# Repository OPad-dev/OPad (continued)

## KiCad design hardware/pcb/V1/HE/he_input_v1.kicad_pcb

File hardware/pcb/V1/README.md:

# OPad V1 PCBs

Modular hardware ecosystem joined by one 8-wire JST-SH cable:

| Board | Folder | Size | Status | What it does |
|---|---|---|---|---|
| **Controller carrier** | `Carrier/` | 35.0 × 48.2 mm, C-shaped | Production | Plugs onto the Waveshare ESP32-S3-Touch-LCD-2 headers and brings the module signals to a connector |
| **MX input module** | `MX/` | 52.0 × 24.0 mm | Production | Two Kailh MX mechanical hot-swap sockets under the key plate |
| **Hall Effect input module** | `HE/` | 52.0 × 24.0 mm | **v2 Experimental** | Two magnetic Rapid Trigger Hall sensors (TI DRV5055) under the key plate |

> [!IMPORTANT]
> The **Hall Effect module** requires firmware v2 (Rapid Trigger support), which is not yet available. V1.1 is built and its sensors work on the bench (2026-10-19, [`docs/specs/v2-hall-effect-design.md`](../../docs/specs/v2-hall-effect-design.md) §10b); the firmware's ADC sampling pipeline and Rapid Trigger engine are specified in [`docs/specs/v2-rapid-trigger.md`](../../docs/specs/v2-rapid-trigger.md). v1 firmware recognises an HE module by its ID voltage, shows a warning on the LCD and ignores key input rather than reading the analog sensor outputs as presses.

The input module is **swappable**: both the MX mechanical module and the Hall-effect (rapid trigger) module use the same outline, mounting holes, connector position and pinout, and plug into the same carrier and cable. The module reports which kind it is through an ID voltage on the connector (0.30 V for MX, 1.06 V for Hall Effect).

Production files live in each board's `production/` folder, one subfolder per fab: `jlcpcb/` (Gerbers, BOM, CPL), `pcbway/` (Gerbers with their order marker, BOM, centroid) and `aisler/` (native KiCad board and ODB++ with the parts in them). Renders, PDFs, STEP and the ERC/DRC reports sit next to them.

Status: the MX module and the carrier pass ERC, DRC and schematic parity in KiCad 10.0.6 with zero errors; the carrier has zero warnings, the MX module only "does not match copy in library" warnings, because its footprint and symbol copies were placed before `lib/` was rewritten by `gen_library.py` (same pads and pins; that board is built and working, so `export_production.py` accepts them). The Hall Effect module is generated and checked by its own toolchain (`scripts/he_board.py`, see below), which needs no KiCad install; it reports zero rule violations, its Gerbers verify clean against the netlist, and the generated KiCad files pass ERC and DRC with schematic parity in KiCad 10.0.6 (`scripts/check_he_kicad.py`; only "footprint does not match library" warnings remain, see Toolchain).

---

## Module connector (JST SH 8-pin, same on every input module)

| Pin | Net | Waveshare pin | GPIO | MX V1 use | Hall module use |
|---|---|---|---|---|---|
| 1 | 3V3 | P2-1 | – | pull-ups, ID divider | sensor supply |
| 2 | GND | P2-2 | – | switch common | ground |
| 3 | IN1 | P1-10 | **GPIO10** (ADC1_CH9) | KEY1 (left key) | analog 1 / SPI CS1 |
| 4 | IN2 | P1-9 | **GPIO7** (ADC1_CH6) | KEY2 (right key) | analog 2 / SPI CS2 |
| 5 | ID | P1-8 | GPIO8 (ADC1_CH7) | ID divider = 0.30 V | own ID voltage |
| 6 | IO6 | P1-3 | GPIO6 (ADC1_CH5) | not used | e.g. SPI MISO |
| 7 | IO4 | P1-2 | GPIO4 (ADC1_CH3) | not used | e.g. SPI MOSI |
| 8 | IO2 | P1-1 | GPIO2 (ADC1_CH1) | not used | e.g. SPI SCK |

- All six signals are ADC1 pins. On the ESP32-S3, ADC continuous (DMA) mode only supports ADC1 (see `docs/specs/v2-rapid-trigger.md` §2.2).
- SPI3 can be routed to any of these pins through the GPIO matrix. None of them are strapping pins, USB, UART0, or the touch/IMU I2C.
- The pin order is chosen so both boards route on two layers with no crossings.
- **Firmware:** in the app, set Key 1 = GPIO10 and Key 2 = GPIO7 (both are already in the allowed pin list). The hand-wired defaults (GPIO14 / GPIO9) don't apply to this board.

### Module ID

Each module has its own divider from 3V3 to GND on ID. The carrier has no parts on this line.

| Module | Top resistor | Bottom resistor | ID voltage |
|---|---|---|---|
| MX V1 | 100 kΩ (R3) | 10 kΩ (R4) | 0.30 V |
| **Hall Effect V1** | **100 kΩ (R1)** | **47 kΩ (R2)** | **1.06 V** |
| reserved: Hall SPI | 100 kΩ | 100 kΩ | 1.65 V |

The divider's source impedance is 100k ∥ 47k ≈ 32 kΩ, above the ~10 kΩ the ESP32-S3 ADC likes. ID is read once at start-up, so average a handful of samples instead of trusting a single conversion.

With no module plugged in, GPIO8 floats. The firmware can enable the internal pull-down to read about 0 V in that case.

---

## MX input module (`MX/`)

- **Case coordinates** below are those of `hardware/3d/custom_case/V1/osupad_enclosure.scad`: origin at the front-left outer corner, X to the right, Y toward the screen. KiCad uses X = 100 + case X and Y = 100 − case Y, so the top of the KiCad editor is the rear of the case and the layout is not mirrored.
- **Key centres:** case (28.475, 16.5) and (47.525, 16.5), 19.05 mm pitch, the same as the plate cutouts.
- **Outline:** case X 12…64, Y 7…31, 1.5 mm corner radius.
- **Mounting holes:** 2× M2 (2.2 mm NPTH) at case (15.5, 16.5) and (60.5, 16.5), on the key axis and clear of the switch footprints. The PCB must be held there, or it moves when a switch is pulled. Case V1.1 does this without screws: pins in the key deck go through the holes and posts on the bottom plate clamp the PCB against the deck.
- **Height:** the PCB top is **5.0 mm below the top of the plate** (plate 1.5 mm, case z = 10.0). About 3.5 mm of free space is needed under the PCB bottom for the sockets (1.85 mm) and J1 (2.9 mm).
- **Everything is on the bottom side** (sockets, J1, R1–R4, C1), so JLCPCB assembles one side only. The switches go in from the top through the plate.
- **J1** sits at the rear edge, centred on the keys, with the opening facing the screen. The cable leaves toward the controller.
- **Footprint:** `lib/osupad.pretty/Kailh_CPG151101S11_MX_Hotswap_Bottom` is the Kailh land pattern (3.05 mm pin holes, 4.0 mm centre, 1.75 mm pegs, 2.55 × 2.5 mm pads), drawn from the socket side and placed flipped. The switch pins point to the rear (standard orientation).

## Hall Effect input module (`HE/`)

Same outline, mounting holes, connector position and pinout as the MX module, so the two are interchangeable on one cable. Instead of switching a pin to ground, each key has a **TI DRV5055A3 ratiometric linear Hall sensor** whose analog output tracks the magnet in the switch stem, which is what rapid trigger needs.

> **V1.0 erratum (fixed in V1.1):** the V1.0 SOT-23 footprint was mirrored, so every assembled sensor sits with **VCC on its IN line and OUT on 3V3**. It powers itself backwards through its protection diode, reads a fixed ~2.9 V and barely reacts to a magnet. The connectivity was right, so neither DRC nor the assembler could catch it. V1.1 swaps pads 1 and 2 (`scripts/gen_library.py`, `scripts/he_board.py`), moves C2/C3 to the pin-1 side so the 3V3 stub and the IN line do not cross, and `he_board.py`'s self-test now checks every SOT-23's pin order against the real package. A V1.0 board works only with each sensor re-soldered upside down (marking towards the board), which mirrors its pin order back.
>
> **V1.1 review (2026-10-10), before ordering:** TI's DBZ pinout (datasheet SBAS640C Figure 4-1 and Table 4-1: 1 = VCC, 2 = OUT, 3 = GND, pin 1 top-left in the top view) was checked against the footprint by hand, against KiCad's flip convention and against the V1.0 measurements; the three agree with the V1.1 pads. Found and fixed in the same pass: the vias grow from 0.6 to **0.7 mm** (0.2 mm annular ring, which Aisler's HASL rules and Eurocircuits' class 6 need; JLCPCB accepted 0.6); the silkscreen square round each sensor was 3.0 mm and crossed the pad tips, it is now 3.6 mm with a pin-1 dot, and `C2`/`C3` moved 0.2 mm away from the sensors to make room; the pour gap went from 0.3 to 0.45 mm and a ground via fills the pocket next to U2, so the Gerbers hold no floating copper slivers (`verify_he_gerbers.py` now checks for islands); the generated schematic had an unescaped quote and did not load in KiCad, so ERC had never actually run on it (it now passes, with PWR_FLAGs and a connector symbol that carries the MP pads). None of these change the netlist.

### Sensor architecture (the part that matters)

This is **Architecture A: bottom-side SMT on solid FR-4.**

- There is **no 4.0 mm stem hole** at the key centres. `SW_MX_Hall_PlateMount` (used for a through-hole stem) is *not* the footprint here; `SW_MX_Hall_PlateMount_SolidCentre` is, and it contributes only the two alignment peg holes.
- U1 and U2 are centred **exactly** on the key centres (16.475, 9.5) and (35.525, 9.5), on the bottom copper, directly under the magnet.
- A **3.0 × 3.0 mm copper keepout on both layers** around each sensor keeps the ground pour out of the magnetic path, so the stem magnet's flux is not damped by eddy currents in the plane. In KiCad these are rule areas with `copperpour not_allowed`; in the Gerbers the pour is genuinely absent there.
### Why there is no centre hole, and what the board is actually compatible with

In a Lekker / Gateron KS-20 class magnetic switch (Gateron's KS-20T drawing DS-02-001-A0, in the [Magnetic Orange datasheet](https://gateron.com/u_file/2312/26/file/GATERONMagneticOrangeSwitch-KS-20TO10B050NW-Y64.pdf), sheet 1):

- **the magnet sits in the stem at the switch centre, N pole towards the PCB.** There is no MX-style centre pole and no 4 mm centre hole;
- **two Ø 1.70 ± 0.05 mm plastic pins, 10.16 mm apart (±5.08 mm), stick out of the bottom and pass straight through the PCB**, protruding about 1 mm out the back. That is why the 1.75 mm peg holes are needed;
- the bottom housing has a pocket ("the hole for setting hall sensor") so Gateron's own reference layout puts a SOT-23 sensor on the **top** of the PCB, between the two pins, with three 0.8 × 0.8 mm pads.

So a top-side sensor is possible with these switches; this board puts it on the bottom instead, like Wooting ([Lekker update #5, part 2](https://wooting.io/post/we-overcame-the-challenges-lekker-update-5-part-22)), because single-side assembly is cheaper and the top of the PCB stays flat against the plate. The price is distance: the magnet reads through the full 1.6 mm of FR-4 plus the package, so the field at the die is a fraction of what Gateron's pocket position sees (numbers under Sensor sensitivity). Peg holes **and** a solid centre **and** a bottom-side sensor is a consistent set; a board that had the peg holes *and* a 4 mm centre hole would be an MX PCB-mount pattern, which is a different switch.

| Switch | Works on this board? |
|---|---|
| Gateron KS-20 / Wooting Lekker, KS-37 / Magnetic Jade, Geon Raw HE and other Lekker-standard magnetic switches | Yes — flush magnet centre, two ±5.08 mm plastic pins |
| Switches sold as "**TMR switches**" | Yes — see below |
| MX mechanical (Cherry, Gateron, Kailh…) | **No.** A real MX switch has a centre pole and metal pins. That is what the `MX/` module is for — same outline, same connector, swap the module |

**On "TMR switches":** TMR (tunnel magnetoresistance) is a *sensor* technology that lives on the keyboard's PCB, not a different kind of switch. A switch marketed as a "TMR switch" is the same magnetic switch — a magnet in an MX-form stem with a flush bottom and two pins — and the industry uses them interchangeably: Gateron Jade, Jade Pro and Lekker V2 all go into Hall boards like the Wooting 60HE and TMR boards like the Womier SK75 alike. This module reads the magnet with a Hall sensor, and the magnet does not know or care what sensor is underneath it, so TMR-branded switches drop straight in.

Two caveats, neither of which is a fit problem:

- **Magnet strength varies by switch model.** TMR sensors are far more sensitive than Hall, so a vendor *can* pair a TMR-targeted switch line with a weaker magnet. If you use such a switch here, A3 is the wrong variant and you want A1 or A2. As Wooting put it, what matters is matching the sensitivity range to the magnet, not chasing sensitivity for its own sake.
- **This board cannot be rebuilt with a TMR sensor as a drop-in.** The common analog TMR parts (MultiDimension TMR2001, TMR2083) are SOT-23-**5**, not the 3-pin SOT-23 used here, so they would need a new footprint and a re-route. Most TMR designs also mount the sensor *off-axis*; U1/U2 here are deliberately on-axis at the key centre, which is the right placement for the DRV5055.

These magnetic switches are deliberately not MX-compatible; vendors say so themselves. The claim this board makes is "every switch in the Lekker standard", not "every keyboard switch ever made". If a magnetic switch turns up with a protruding MX-style centre pole, it will foul the sensor and is out of scope for V1 — I found no current HE switch that does this, since the whole class puts the magnet where that pole would be.

### Sensor sensitivity

The magnet reads through 1.6 mm of FR-4, so the field at the die is weaker than a top-side design's. Wooting hit the same geometry and compensated with a stronger magnet *and* a more sensitive sensor. All three variants share the SOT-23 pinout and this footprint, so **the board never changes** — only which reel JLCPCB loads. Set `SENSOR_VARIANT` in `scripts/he_board.py` and regenerate.

Datasheet values (TI SBAS640C §5.6, VCC = 3.3 V, 25 °C): quiescent output 1.59–1.71 V (typ. 1.65 V), linear output range 0.2 V to VCC − 0.2 V, input-referred noise 0.2 mT peak-to-peak for every variant (so a more sensitive part gives more volts per millimetre but the same magnetic noise):

| Variant | LCSC | Sensitivity @3.3 V | Linear range @3.3 V | Notes |
|---|---|---|---|---|
| A1 | `C962987` | 60 mV/mT (57–63) | ±22 mT | clips before mid-travel with a Jade |
| A2 | `C266131` | 30 mV/mT (28.5–31.5) | ±44 mT | about 2× A3's resolution, may clip in the last few tenths of a millimetre |
| A3 | `C266128` | 15 mV/mT (14.3–15.8) | ±88 mT | current default; cannot clip |

What the magnet delivers: Gateron quotes the Magnetic Jade at 120 Gs (12 mT) initial and 700–800 Gs (70–80 mT) at bottom-out "with a 1.2 mm PCB", N pole towards the PCB; the KS-20T, read in its pocket, at 102 / 905 Gs. Through 1.6 mm the bottom-out figure drops to very roughly 50–60 mT. With the N pole facing the sensor's back the output **rises** when the key is pressed: A3 goes from about 1.8 V at rest to about 2.4–2.6 V at bottom-out, inside the ESP32-S3 ADC's accurate range at 12 dB (0–2.9 V, ±50 mV); A2 would reach 3.1 V (its limit) at 48 mT, so it saturates near the end of travel but doubles the resolution over the rest. A3 is shipped as the default because it cannot saturate, which makes first bring-up unambiguous; the first V1.1 build measured about 1.80 V at rest and +568 mV at a hard bottom-out (≈ 2.37 V, design doc §10b), so A3 stays. The Jade Silent (3.2 ± 0.2 mm travel) has no published flux figures.

### Layout

- **Everything is on the bottom side**, so JLCPCB assembles one side.
- `U1`/`U2` are at 180°, so both analog outputs face the connector and both ground pads face the board's front edge, where a short stub and a via drop them into the pour outside the keepout.
- `C2`/`C3` sit just outside each keepout on the pin-1 side (centre 2.7 mm from the sensor, 100 nF; TI asks for at least 10 nF close to VCC, §7.4), feeding VCC from the side; `C1` is the bulk decoupler next to J1 pin 1.
- **3V3 is distributed on F.Cu**, the otherwise empty top layer, so every analog trace stays on B.Cu with no crossings. Four vias tie it to the bottom-side stubs.
- `R1`/`R2` are the 100 k / 47 k ID divider.
- J1-6/7/8 (GPIO6/4/2) are reserved for an SPI variant, so instead of being left floating they run to probe pads **TP1/TP2/TP3** below the connector — the three bare pads visible under J1 in the render. They are board features, not parts: nothing is assembled on them, they take no solder paste, and they appear in neither the BOM nor the centroid file. Delete `_probe_pad(...)` from `PARTS` in `he_board.py` and regenerate if you would rather leave those pins unconnected.
- Ground: pours on both layers with a 0.45 mm gap to foreign copper (wide enough that no sliver is left between 1.0 mm pitch traces), thermal relief on every ground pad, and 22 plated vias stitching the two planes.
- Vias are 0.7 mm with a 0.3 mm hole (0.2 mm annular ring), tented on both sides.

### Pinout

| Pin | Net | Goes to |
|---|---|---|
| 1 | 3V3 | U1-1, U2-1 (VCC), C1/C2/C3, R1 |
| 2 | GND | ground pours, U1-3, U2-3, C1/C2/C3, R2 |
| 3 | IN1 | U1-2 (OUT), key 1 analog → GPIO10 (ADC1_CH9) |
| 4 | IN2 | U2-2 (OUT), key 2 analog → GPIO7 (ADC1_CH6) |
| 5 | ID | R1/R2 divider, 1.06 V → GPIO8 (ADC1_CH7) |
| 6, 7, 8 | IO6 / IO4 / IO2 | TP1 / TP2 / TP3 probe pads, reserved for SPI |

**DRV5055 SOT-23 pinout: 1 = VCC, 2 = OUT, 3 = GND** (TI DBZ package, datasheet Figure 4-1 and Table 4-1). Worth repeating because swapping 2 and 3 would put the output straight on ground. Turned so pins 1–2 face up, pin 1 is on the **right** in the top view of the chip; a chip on the bottom side is seen mirrored from above, so in the board's top view (and in the KiCad editor) pad 1 is the **left** one of the pair, the one next to the silkscreen dot. `he_board.py`'s self-test enforces this and also compares J1's pinout with the built MX board and the sensor symbol's pin names with the nets.

### Toolchain

The HE board does not depend on a KiCad install. `scripts/he_board.py` holds the geometry, netlist and placement, and checks its own design rules; everything else is derived from it:

```
python3 scripts/he_board.py            # placement self-test + DRC, exit 1 on any violation
python3 scripts/generate_he_gerbers.py # Gerbers, drills, job file, BOM, CPL (JLCPCB + PCBWay)
python3 scripts/generate_he_kicad.py   # .kicad_sch, .kicad_pcb, .kicad_pro, lib tables
python3 scripts/verify_he_gerbers.py   # rasterise the Gerbers, check nets for opens/shorts/islands
python3 scripts/render_he_preview.py   # production/*-top.png and *-bottom.png
python3 scripts/check_he_kicad.py      # optional, needs kicad-cli: ERC + DRC (zones refilled, parity)
```

`generate_he_gerbers.py` and `generate_he_kicad.py` both refuse to write anything if the DRC fails. `verify_he_gerbers.py` does not re-read the geometry and declare it fine: it replays the Gerber files, including every clear-polarity knockout, labels the copper regions, joins the layers through the vias, and then asserts that each net is one region and that no region carries two nets. It also checks that the sensor keepouts hold no pour copper, that nothing sits over a non-plated hole, and that every copper region holds a pad or a via (no floating slivers, which this writer has no minimum-width pass to remove). Both it and the preview renderer need Pillow.

`check_he_kicad.py` is the independent second opinion: KiCad's ERC on the schematic and DRC on the board with the zones refilled and schematic parity on. It reports warnings and fails on errors. The warnings it leaves are "footprint does not match copy in library" for every part, which is expected: the board carries the library footprints without their silkscreen, because the board's silkscreen (sensor squares, pin-1 dots, labels) comes from `he_board.py` and is the same drawing the Gerbers get.

Copper pours in the Gerbers are real: the pour is filled, then every foreign pad, track, via and NPTH is knocked out with `%LPC*%` using apertures grown by the 0.45 mm pour gap, then the actual copper is flashed back. Isolation gaps show up properly in any fab viewer.

**File format:** the board is written in KiCad 8 syntax (`version 20240108`), which KiCad 8, 9 and 10 all open. The schematic is KiCad 9 syntax, because it embeds the shared symbol library and that library is saved by KiCad 10; it uses `Conn_01x08_1MP` (the connector with its mounting pads as pin MP, on GND) and two `PWR_FLAG`s so ERC and parity are clean. This differs from `MX/` and `Carrier/`, which are native KiCad 10 files. Zones are written as outlines with their clearance and thermal settings; KiCad fills them on open (or any DRC run) — the shipped Gerbers already contain the filled result.

Running `scripts/generate_boards.py` under KiCad's Python regenerates MX and the carrier with `pcbnew` as before; its `build_he()` just calls the generator above, so there is only one definition of this board.

## Controller carrier (`Carrier/`)

- **Outline:** the Waveshare PCB (35.0 × 48.2 mm) with a **22.8 × 34.7 mm window**, open at the USB-C end. The TF card slot, the MX1.25 battery connector and the camera FPC stay reachable.
- **Headers** (from the Waveshare STEP model and drawing):
  - The rows are 30.48 mm apart, 2.26 mm from each long edge.
  - Pin 1 is 7.59 mm from the non-USB edge, 2.54 mm pitch.
- **Seen from the carrier's top** (the side marked `WAVESHARE ON THIS SIDE`): P1 (GPIO2 … 5V) is on the right and P2 (3V3 … VBAT) on the left, both with pin 1 at the non-USB end. This is the mirror image of Waveshare's back-side pinout photo, as it must be.
- **Holes:** 4× M2 at the Waveshare hole positions (29.0 × 42.2 mm, 3.0 mm from the edges).
- **Sockets:** 2× 1×14 female, 8.5 mm tall, soldered on the top side. J_MOD (JST SH) is on the bottom at the non-USB end, opening outward.
- **Free for later:** P1-11/12/13/14 (USB D+, D−, GND, 5V) are on the rail at the USB-C end, unused, ready for an internal USB-C board (still under discussion).
- **Antenna:** there is no copper pour under the bridge, which sits below the Waveshare's ceramic antenna.

### Stack height

| From | To | Distance |
|---|---|---|
| Waveshare PCB back | carrier top | 11.0 mm (2.5 mm male-header plastic + 8.5 mm socket) |
| carrier top | carrier bottom | 1.6 mm |
| carrier bottom | J_MOD bottom (non-USB end only) | 2.9 mm |
| carrier bottom | socket pin tails | about 3 mm; clip them flush after soldering |
| glass front | carrier bottom | about 19.8 mm |

**Use case V1.1** ([`hardware/3d/custom_case/V1.1`](../../3d/custom_case/V1.1/README.md)). The V1 case does not fit this stack: with its 20.3° deck, the carrier's lower long edge reaches the floor and the Waveshare support pillars are in the way. V1.1 does the following:
- tilts the screen at 16° in a raised pod, with the stack 0.6 mm above the floor at its lowest point;
- replaces the pillars with posts under the carrier's M2 holes;
- mounts the input module without screws: pins in the key deck locate it and the bottom plate clamps it;
- routes the cable from the carrier's left end along the left wall to the module's J1 (a 100 mm cable is enough).

---

## Ordering

### Bare PCBs (JLCPCB or PCBWay)

Upload `production/jlcpcb/<board>-gerbers.zip` (JLCPCB) or `production/pcbway/<board>-gerbers-PCBWay.zip` (PCBWay). All boards use standard options:

| Option | Value |
|---|---|
| Layers | 2 |
| Thickness | 1.6 mm (keep it: the Kailh socket and 5.0 mm plate-to-PCB distance assume 1.6 mm) |
| Copper | 1 oz |
| Min track / clearance | 0.25 / 0.2 mm |
| Min drill | 0.3 mm (vias) |
| Via | 0.6 mm (MX, carrier) / 0.7 mm (HE), 0.3 mm hole |
| Finish | HASL lead-free or ENIG |

European fabs: the HE module fits Aisler's "2 layer 1.6 mm HASL" rules (track 0.2, spacing 0.15, drill ≥ 0.3, via ring 0.2, copper to edge 0.3, hole to hole 0.3) and Eurocircuits pattern class 6 / drill class C (track and isolation 0.15, outer ring 0.125 measured from the 0.4 mm production tool, non-plated hole isolation 0.2). Checked against their published tables on 2026-10-10; the MX and carrier vias (0.6 mm) give a 0.15 mm ring, which Aisler HASL does not accept, so order those two with ENIG there or enlarge their vias first.
| Order number | "Specify a location" (JLCPCB): each board has a `JLCJLCJLCJLC` silkscreen mark on the bottom |

The Gerbers include the board outline on its own layer (the carrier's window and corner radii are in Edge.Cuts) plus separate PTH and NPTH drill files.

### Assembly (JLCPCB)

Upload `production/jlcpcb/<board>-BOM-JLCPCB.csv` and `production/jlcpcb/<board>-CPL-JLCPCB.csv`.

**MX module**: assembly side **Bottom**.

| Designator | Part | LCSC |
|---|---|---|
| SW1, SW2 | Kailh CPG151101S11 MX hot-swap socket | C41430893 |
| J1 | JST SM08B-SRSS-TB | C160407 |
| R1, R2, R4 | 10 kΩ 1 % 0603 | C25804 |
| R3 | 100 kΩ 1 % 0603 | C25803 |
| C1 | 100 nF 50 V X7R 0603 | C14663 |

**Hall Effect module**: assembly side **Bottom**.

| Designator | Part | LCSC |
|---|---|---|
| U1, U2 | TI DRV5055A3QDBZR linear Hall sensor, SOT-23 | C266128 |
| J1 | JST SM08B-SRSS-TB | C160407 |
| C1, C2, C3 | 100 nF 50 V X7R 0603 | C14663 |
| R1 | 100 kΩ 1 % 0603 | C25803 |
| R2 | 47 kΩ 1 % 0603 | C25819 |

TP1–TP3 are bare probe pads; they are board features, not parts, and are absent from the BOM and centroid file. U1/U2 are an **Extended** LCSC part, so JLCPCB adds the one-off feeder charge.

> Two part numbers that circulate for this board are wrong and were corrected here: **C2843516 is a Schottky diode** (Jingdao SSL310F), not the DRV5055 — the sensor is **C266128**. And **C25816 is a 383 kΩ resistor**, not 47 kΩ — the 47 kΩ `0603WAF4702T5E` is **C25819**. Building from the older numbers would populate a diode where the Hall sensor goes and put the ID line at 3.3 V × 383/483 = 2.62 V, which the firmware would not recognise as this module.

**Carrier**:

| Designator | Part | LCSC |
|---|---|---|
| J_MOD | JST SM08B-SRSS-TB, bottom side | C160407 |
| J_P1, J_P2 | 1×14 female header, 2.54 mm, 8.5 mm, top side (THT) | C2897377 |

The CPL gives the two sockets at their **centre, rotated 90°**, because JLCPCB's model of C2897377 is centred and lies along X. KiCad's own position file puts them at pin 1 with 0°, and JLCPCB's preview then shows one socket lying across the board. `export_production.py` applies this correction (`JLC_CPL_FIXES`). The socket is symmetric, so 90° and 270° give the same part.

J_MOD is the only SMD part, on the bottom. The two sockets are through-hole on the top: order them assembled as THT, or solder them yourself (plug them onto the Waveshare board while soldering so they stay aligned).

**Check the part rotation in JLCPCB's placement preview before paying.** KiCad and LCSC define rotation differently for some parts, most often the Kailh socket, the JST connector and SOT-23 parts:
- the socket's two pads must cover the two copper pads next to the 3.05 mm holes;
- the JST's 8 contacts sit toward the inside of the board, with the plug opening at the board edge;
- on the HE module U1 and U2 are at **180°**: the single lead (pin 3, GND) must point toward the board's front edge (the `OSUPAD HE` text), the two-lead side (pins 1 and 2) toward the connector, inside the silkscreen square. JLCPCB's preview shows the bottom as seen from below; with the connector edge away from you, pin 1 (VCC) is then the **right-hand** lead of the pair, next to the silkscreen dot. A SOT-23 cannot be placed mirrored, so if the pins sit on the pads the orientation is right; if a sensor shows rotated 90° or 180° with its leads off the pads, rotate it in the preview. Both sensors face the same way, so if one looks wrong they both are.

### AISLER

AISLER reads the parts from a native board file or ODB++ and wants no BOM or centroid file. `scripts/export_aisler.py` writes `<board>/production/aisler/` for every board: `<board>.kicad_pcb` with the zones filled and saved by KiCad, the `JLCJLCJLCJLC` order text removed and `MPN` / `MFG` as separate fields (upload this single file); `<board>-odb.zip`, the same board as ODB++ (the alternative); the schematic PDF; a BOM for checking by eye; a `README.txt` with the order options; and `<board>-aisler.zip` holding all of them. `MPN` is the bare part number, the field AISLER matches on. On the HE module TP1–TP3, the holes and the switch positions are excluded from the BOM and marked DNP so they do not show up as parts. The copy passes KiCad's DRC with the project's rules before it is written. Order as 2 layers, 1.6 mm; the HE module's 0.7 mm vias meet their HASL rules, the MX and carrier's 0.6 mm vias (0.15 mm ring) do not, so order those with ENIG or ask.

### PCBWay

Use the files in `production/pcbway/`, not the `jlcpcb/` ones:
- `<board>-gerbers-PCBWay.zip`: the order-number marker is `WayWayWay` instead of `JLCJLCJLCJLC`.
- `<board>-BOM-PCBWay.csv`: PCBWay's BOM template columns, with manufacturer, part number, type (SMD/THT) and placement notes.
- `<board>-centroid-PCBWay.csv`: placement file.

Order each board as a separate item.

### Loose parts (not on the PCBs)

| Qty | Part | Note |
|---|---|---|
| 1 | JST SH 1.0 mm 8-pin cable, 100 mm, **same-direction** (pin 1 ↔ pin 1) | Many cheap "reverse" cables swap pin 1 ↔ 8: check with a multimeter before plugging in |
| 2 | MX switches (3- or 5-pin) + keycaps | MX module |
| 2 | MX magnetic switches (Gateron KS-20, Magnetic Jade, Wooting Lekker, Geon Raw HE) + keycaps | HE module |
| 1 | 14 × 14 mm switch plate, 1.5 mm, held 5.0 mm above the PCB | both modules; the HE module needs it, since the switches are plate-mounted and nothing holds them to the PCB |
| 4 | M2 spacers, 8.5 mm (or 8 mm + washer), optional | Carrier to the Waveshare standoffs; the sockets hold a first prototype on their own |

## Before the first order

1. Print `production/<board>-pcb.pdf` at 100 % and lay the Waveshare board and two switches on it. The HE module has no PDF; use `production/he_input_v1-bottom.png` (2240 px wide = 52.0 mm, so print it at 1094 dpi for 1:1) or open the `.kicad_pcb`.
2. In the JLCPCB preview, check socket, connector and SOT-23 rotation (see above).
3. Check the cable direction with a multimeter.
4. Order 5 of each and test-fit before a larger batch.
5. For the HE module, measure before committing to a batch: probe IN1/IN2 with the switch at rest and fully pressed. If the swing is much under ~0.5 V, move to a DRV5055A2 or A1 (drop-in, same footprint) rather than respinning the board.

## Testing the assembled boards

With the Waveshare on the carrier, the MX module on the cable and the pad
connected, run `opadctl board-test` or open **Diagnostics → PCB Test** in the
app. Release both keys while it runs. The pad checks
(`firmware/main/diag/board_test.c`, judged in
`desktop/crates/opad-model/src/board_test.rs`):

| Check | How | Typical faults it finds |
|---|---|---|
| Input module | ID voltage on GPIO8, 0.30 V for MX | Cable unplugged; P2-1 / P2-2 / P1-8 sockets not soldered; R3/R4 wrong |
| Cable | Pulls GPIO2 up: on a reversed cable this powers the module's IN2 pull-up onto ID | A pin 1 ↔ 8 "reverse" JST cable |
| Key pins | Keys must be GPIO10 / GPIO7 with the carrier | Old hand-wired pins (the app and `--fix-pins` set them) |
| Key 1 / Key 2 line | Swaps the pad's pull-up for a pull-down: R1/R2 (10 kΩ) must still hold the line high | Open line (cable, J1/J_MOD pin 3/4, socket P1-10/P1-9, R1/R2); line shorted to GND |
| Spare lines | Connector pins 6–8 must follow the pad's pulls, and must not follow a driven neighbour | Solder bridges on J_MOD or J1 |

It does not press the switches for you: afterwards, press each key in
Diagnostics → Switch Chatter & Input (or watch the counters in `opadctl status`).
Key 1 and Key 2 must each register on their own.

---

## Files

```
V1/
├── lib/                      project library shared by all boards
│   ├── osupad.kicad_sym      R, C, SW_Push, DRV5055, Conn_01x08, Conn_01x08_1MP, Conn_01x14, TestPoint, PWR_FLAG
│   └── osupad.pretty/        0603 R/C, SOT-23, JST SH, pin socket, M2 hole, Kailh hot-swap, Hall switch positions, test pad
├── Carrier/                  controller_carrier_v1.kicad_pro / .kicad_sch / .kicad_pcb, production/
├── MX/                       mx_input_v1.kicad_pro / .kicad_sch / .kicad_pcb, production/
├── HE/                       he_input_v1.kicad_pro / .kicad_sch / .kicad_pcb, production/
├── mechanical_reference_case_coords.dxf   case, plate cutouts, input PCB outline/holes/J1 (case coordinates)
└── scripts/
    ├── gen_library.py           writes the standard parts in lib/ (symbols, 0603 R/C, SOT-23, JST SH, pin socket, M2 hole)
    ├── generate_boards.py       generator for projects (see below)
    ├── export_production.py     ERC + DRC + parity check, then Gerbers, drills, BOM, CPL, PDFs, STEP, renders
    ├── he_board.py              HE module: geometry, netlist, placement and its own DRC (no KiCad needed)
    ├── generate_he_gerbers.py   HE module: Gerbers, drills, job file, BOM, CPL
    ├── generate_he_kicad.py     HE module: .kicad_sch / .kicad_pcb / .kicad_pro
    ├── verify_he_gerbers.py     HE module: rasterise the Gerbers, check the netlist for opens/shorts/islands
    ├── render_he_preview.py     HE module: top/bottom artwork previews
    ├── check_he_kicad.py        HE module: KiCad ERC + DRC (parity) through kicad-cli, optional
    ├── export_aisler.py         every board: filled native board + ODB++ for AISLER (reads parts from the board)
    └── strokefont.py            single-stroke vector font for generated silkscreen
```

The shared library gained two footprints and three symbols for this module: `SW_MX_Hall_PlateMount_SolidCentre` (peg holes only, no stem hole), `TestPoint_Pad_1.0x1.0mm`, and the `TestPoint`, `Conn_01x08_1MP` and `PWR_FLAG` symbols.

Each `production/` folder contains `-schematic.pdf`, `-pcb.pdf`, `.step` (for the case CAD), top/bottom renders and the ERC/DRC reports, plus one subfolder per fab: `jlcpcb/` (`-gerbers.zip`, `-BOM-JLCPCB.csv`, `-CPL-JLCPCB.csv`), `pcbway/` (`-gerbers-PCBWay.zip`, `-BOM-PCBWay.csv`, `-centroid-PCBWay.csv`) and `aisler/` (native board, ODB++, `-aisler.zip`; see Ordering).

- **Regenerating:** `python3 hardware/pcb/V1/scripts/generate_boards.py` rebuilds the schematics and boards from the netlist in the script and overwrites any edits made in KiCad. After editing in KiCad, only run `export_production.py` (JLCPCB and PCBWay files, PDFs, STEP, renders) and `export_aisler.py`. Both export every board by default. Pass board folders to export only those, e.g. `export_production.py Carrier`.
- **Requirements:** KiCad 10 (`kicad-cli` and the `pcbnew` Python module) for MX and the carrier. The KiCad libraries don't need to be installed: everything used is in `lib/`.
- **Library:** every part in `lib/` is OPad's own drawing under the hardware's CERN-OHL-S-2.0 licence (`hardware/LICENSE`). The standard parts are written by `scripts/gen_library.py` (pads and pins from the component datasheets; outlines, silkscreen, courtyards and symbol graphics computed by the script); edit the tables there and re-run it rather than editing those files in KiCad. The Kailh hot-swap, Hall switch and test-pad footprints are hand-drawn. Footprints reference KiCad's installed 3D models by path (`${KICAD10_3DMODEL_DIR}`); the models themselves are not in this repository.
- **The HE module is the exception:** it is generated and verified with plain Python (3.9+), no KiCad and no `pcbnew`; Pillow is needed only for `verify_he_gerbers.py` and `render_he_preview.py`, and `kicad-cli` only for the optional `check_he_kicad.py`. Its `production/` folder has no `drc.json`/`erc.json`/PDF/STEP, because those come from `kicad-cli`; run `export_production.py` under a KiCad install if you want them. CI does not run the HE scripts; run them by hand before ordering.

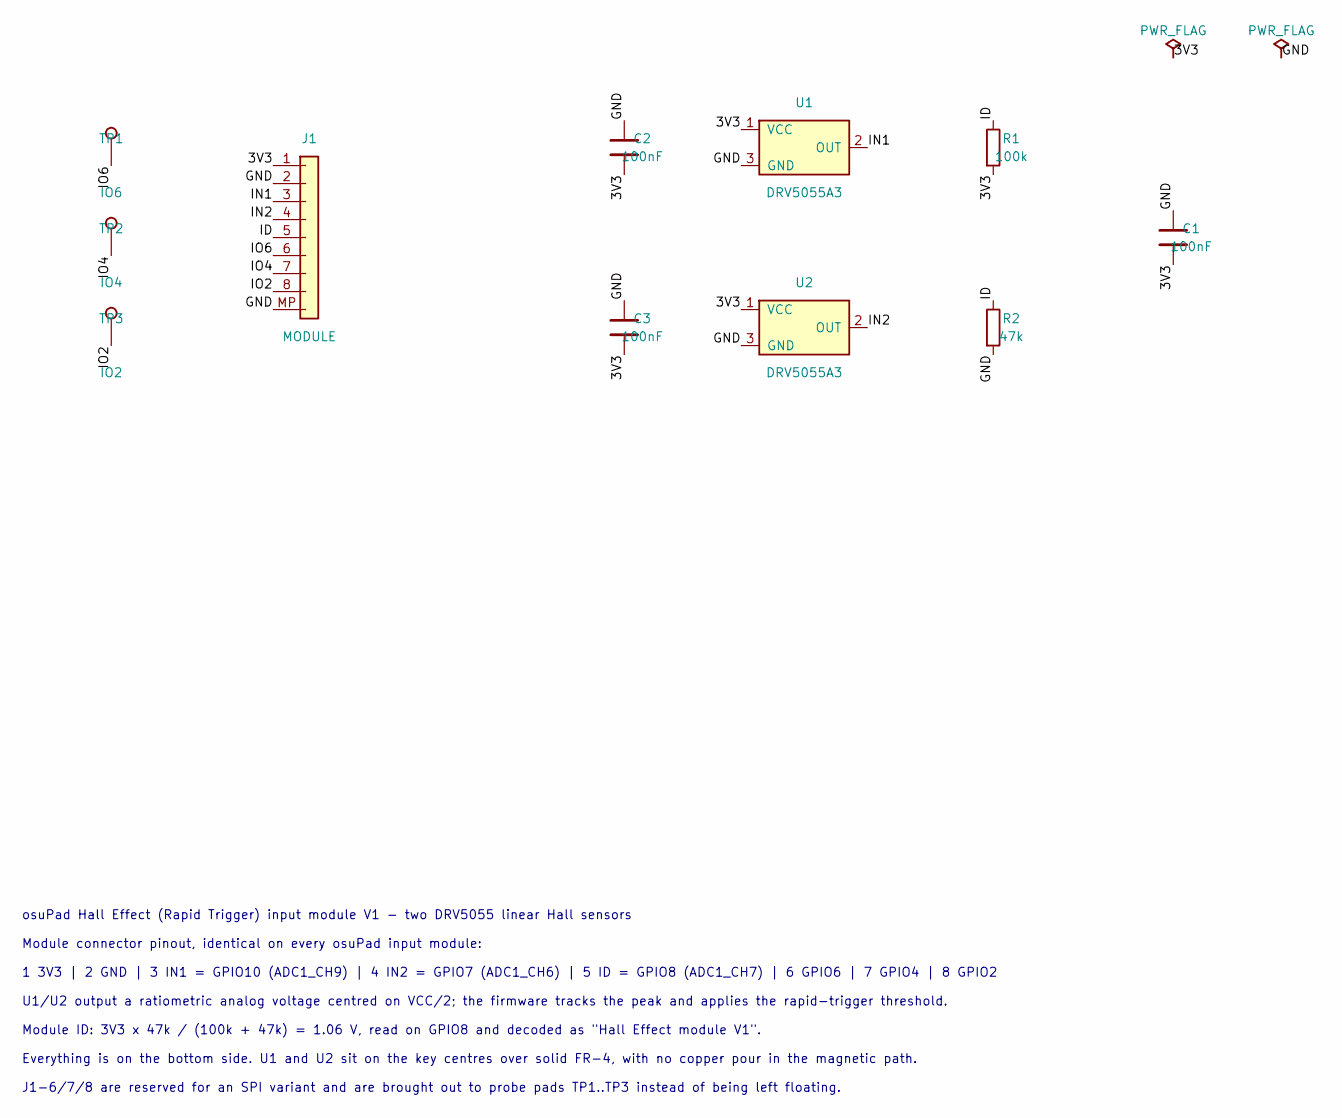
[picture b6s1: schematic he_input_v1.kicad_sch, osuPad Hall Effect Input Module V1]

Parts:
C1, C2, C3: 100nF; C_0603_1608Metric; MPN CC0603KRX7R9BB104; LCSC C14663
J1: MODULE; JST_SH_SM08B-SRSS-TB_1x08-1MP_P1.00mm_Horizontal; MPN SM08B-SRSS-TB(LF)(SN); LCSC C160407
R1: 100k; R_0603_1608Metric; MPN 0603WAF1003T5E; LCSC C25803
R2: 47k; R_0603_1608Metric; MPN 0603WAF4702T5E; LCSC C25819
TP1: IO6; TestPoint_Pad_1.0x1.0mm
TP2: IO4; TestPoint_Pad_1.0x1.0mm
TP3: IO2; TestPoint_Pad_1.0x1.0mm
U1, U2: DRV5055A3; SOT-23; MPN DRV5055A3QDBZR; LCSC C266128

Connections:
/3V3: C1.2, C2.2, C3.2, J1.1, R1.2, U1.1 (VCC), U2.1 (VCC)
/GND: C1.1, C2.1, C3.1, J1.2, J1.MP, R2.2, U1.3 (GND), U2.3 (GND)
/ID: J1.5, R1.1, R2.1
/IN1: J1.3, U1.2 (OUT)
/IN2: J1.4, U2.2 (OUT)
/IO2: J1.8, TP3.1
/IO4: J1.7, TP2.1
/IO6: J1.6, TP1.1

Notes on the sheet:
osuPad Hall Effect (Rapid Trigger) input module V1 - two DRV5055 linear Hall sensors
Module connector pinout, identical on every osuPad input module:
1 3V3 | 2 GND | 3 IN1 = GPIO10 (ADC1_CH9) | 4 IN2 = GPIO7 (ADC1_CH6) | 5 ID = GPIO8 (ADC1_CH7) | 6 GPIO6 | 7 GPIO4 | 8 GPIO2
U1/U2 output a ratiometric analog voltage centred on VCC/2; the firmware tracks the peak and applies the rapid-trigger threshold.
Module ID: 3V3 x 47k / (100k + 47k) = 1.06 V, read on GPIO8 and decoded as "Hall Effect module V1".
Everything is on the bottom side. U1 and U2 sit on the key centres over solid FR-4, with no copper pour in the magnetic path.
J1-6/7/8 are reserved for an SPI variant and are brought out to probe pads TP1..TP3 instead of being left floating.

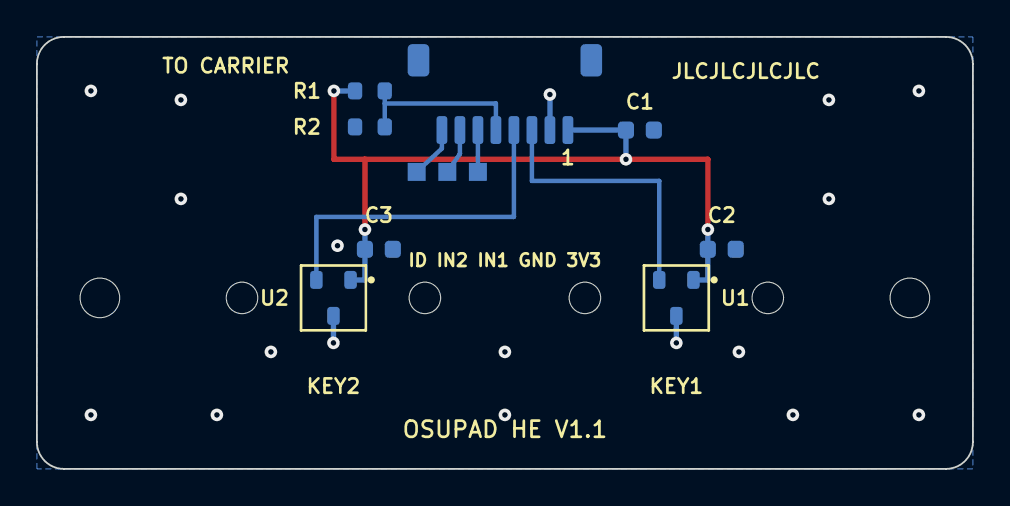
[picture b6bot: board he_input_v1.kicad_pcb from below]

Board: 2 copper layers, 52.0 x 24.0 mm, 15 parts (13 on the bottom side), 8 nets.

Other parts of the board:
H1, H2: MountingHole_2.2mm_M2
SW1: KEY1; SW_MX_Hall_PlateMount_SolidCentre
SW2: KEY2; SW_MX_Hall_PlateMount_SolidCentre

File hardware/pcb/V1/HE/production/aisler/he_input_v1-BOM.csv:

Reference,Quantity,Value,Footprint,MFG,MPN,LCSC,Side,Type
"U1,U2",2,DRV5055A3,SOT-23,Texas Instruments,DRV5055A3QDBZR,C266128,bottom,SMD
"C2,C3,C1",3,100nF,C_0603_1608Metric,YAGEO,CC0603KRX7R9BB104,C14663,bottom,SMD
"J1",1,MODULE,JST_SH_SM08B-SRSS-TB_1x08-1MP_P1.00mm_Horizontal,JST,SM08B-SRSS-TB(LF)(SN),C160407,bottom,SMD
"R1",1,100k,R_0603_1608Metric,UNI-ROYAL,0603WAF1003T5E,C25803,bottom,SMD
"R2",1,47k,R_0603_1608Metric,UNI-ROYAL,0603WAF4702T5E,C25819,bottom,SMD

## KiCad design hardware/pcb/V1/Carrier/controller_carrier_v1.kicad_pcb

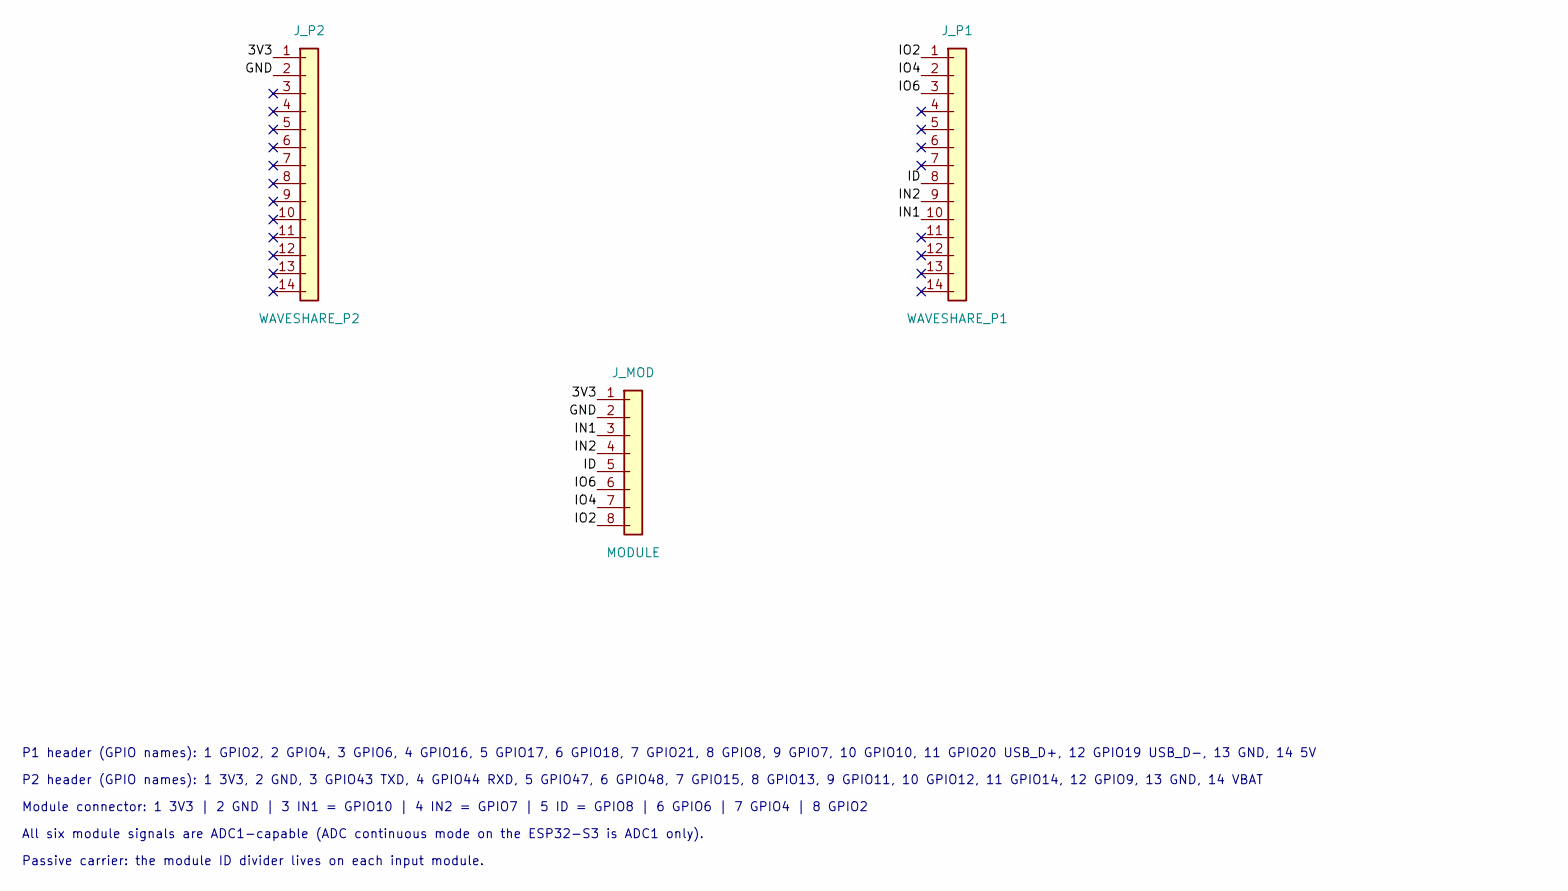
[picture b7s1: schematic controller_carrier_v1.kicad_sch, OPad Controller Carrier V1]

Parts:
J_MOD: MODULE; JST_SH_SM08B-SRSS-TB_1x08-1MP_P1.00mm_Horizontal; MPN JST SM08B-SRSS-TB(LF)(SN); LCSC C160407
J_P1: WAVESHARE_P1; PinSocket_1x14_P2.54mm_Vertical; MPN HCTL PM254-1-14-Z-8.5; LCSC C2897377
J_P2: WAVESHARE_P2; PinSocket_1x14_P2.54mm_Vertical; MPN HCTL PM254-1-14-Z-8.5; LCSC C2897377

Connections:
/3V3: J_MOD.1, J_P2.1
/GND: J_MOD.2, J_P2.2
/ID: J_MOD.5, J_P1.8
/IN1: J_MOD.3, J_P1.10
/IN2: J_MOD.4, J_P1.9
/IO2: J_MOD.8, J_P1.1
/IO4: J_MOD.7, J_P1.2
/IO6: J_MOD.6, J_P1.3

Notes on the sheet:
P1 header (GPIO names): 1 GPIO2, 2 GPIO4, 3 GPIO6, 4 GPIO16, 5 GPIO17, 6 GPIO18, 7 GPIO21, 8 GPIO8, 9 GPIO7, 10 GPIO10, 11 GPIO20 USB_D+, 12 GPIO19 USB_D-, 13 GND, 14 5V
P2 header (GPIO names): 1 3V3, 2 GND, 3 GPIO43 TXD, 4 GPIO44 RXD, 5 GPIO47, 6 GPIO48, 7 GPIO15, 8 GPIO13, 9 GPIO11, 10 GPIO12, 11 GPIO14, 12 GPIO9, 13 GND, 14 VBAT
Module connector: 1 3V3 | 2 GND | 3 IN1 = GPIO10 | 4 IN2 = GPIO7 | 5 ID = GPIO8 | 6 GPIO6 | 7 GPIO4 | 8 GPIO2
All six module signals are ADC1-capable (ADC continuous mode on the ESP32-S3 is ADC1 only).
Passive carrier: the module ID divider lives on each input module.

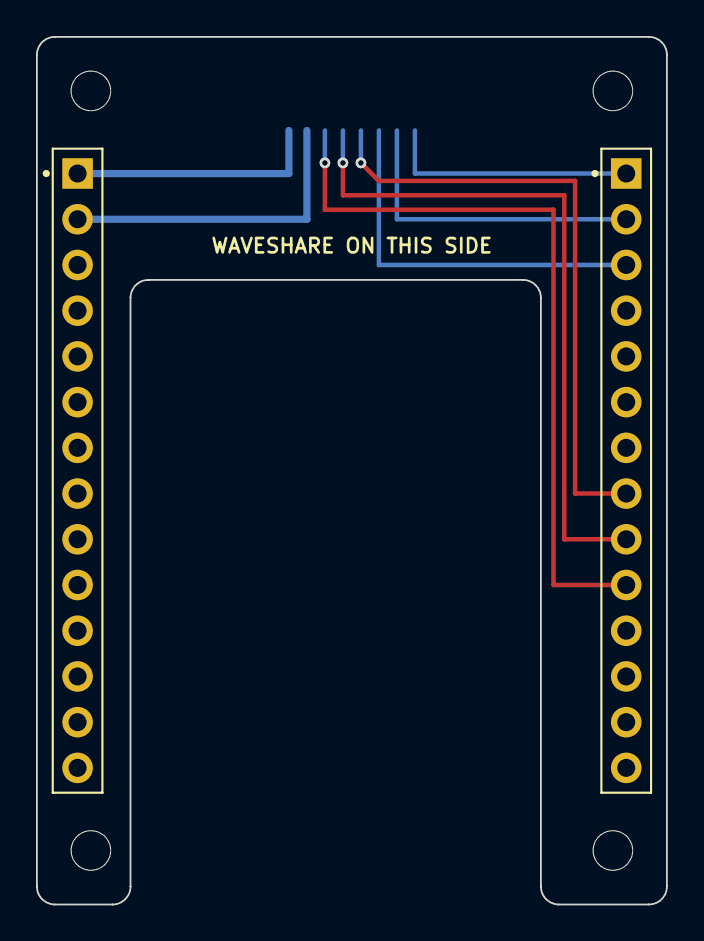
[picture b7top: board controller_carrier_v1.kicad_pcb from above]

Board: 2 copper layers, 35.0 x 48.2 mm, 7 parts (1 on the bottom side), 8 nets.

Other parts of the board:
H1, H2, H3, H4: MountingHole_2.2mm_M2

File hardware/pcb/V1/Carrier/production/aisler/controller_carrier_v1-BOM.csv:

Reference,Quantity,Value,Footprint,MFG,MPN,LCSC,Side,Type
"J_P2",1,WAVESHARE_P2,PinSocket_1x14_P2.54mm_Vertical,HCTL,PM254-1-14-Z-8.5,C2897377,top,THT
"J_P1",1,WAVESHARE_P1,PinSocket_1x14_P2.54mm_Vertical,HCTL,PM254-1-14-Z-8.5,C2897377,top,THT
"J_MOD",1,MODULE,JST_SH_SM08B-SRSS-TB_1x08-1MP_P1.00mm_Horizontal,JST,SM08B-SRSS-TB(LF)(SN),C160407,bottom,SMD

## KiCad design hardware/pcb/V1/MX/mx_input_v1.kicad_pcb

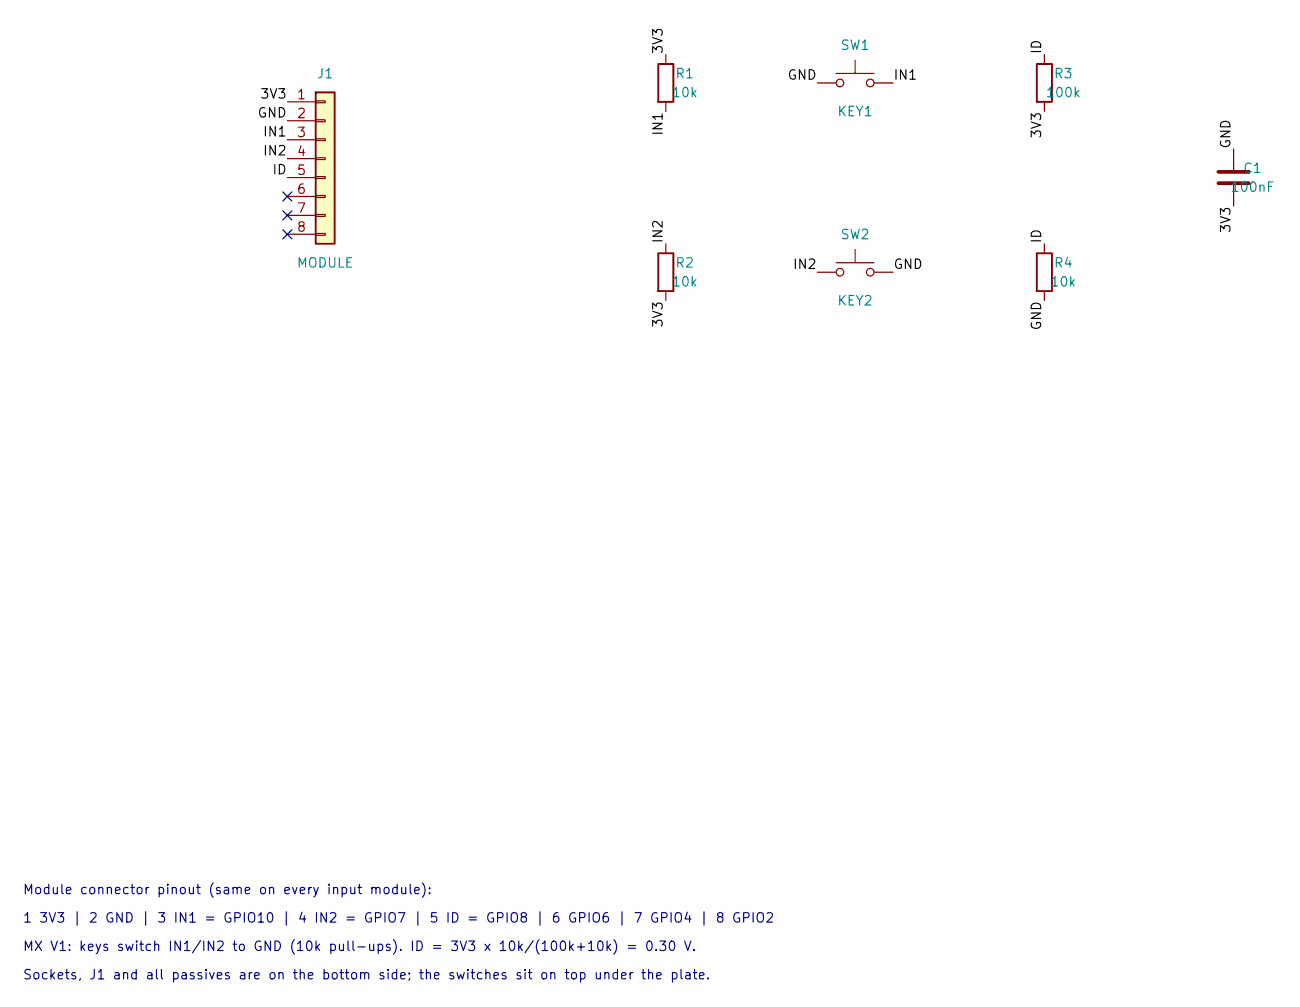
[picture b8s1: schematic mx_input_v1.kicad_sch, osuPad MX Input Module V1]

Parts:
C1: 100nF; C_0603_1608Metric; MPN YAGEO CC0603KRX7R9BB104; LCSC C14663
J1: MODULE; JST_SH_SM08B-SRSS-TB_1x08-1MP_P1.00mm_Horizontal; MPN JST SM08B-SRSS-TB(LF)(SN); LCSC C160407
R1, R2, R4: 10k; R_0603_1608Metric; MPN UNI-ROYAL 0603WAF1002T5E; LCSC C25804
R3: 100k; R_0603_1608Metric; MPN UNI-ROYAL 0603WAF1003T5E; LCSC C25803
SW1: KEY1; Kailh_CPG151101S11_MX_Hotswap_Bottom; MPN Kailh CPG151101S11; LCSC C41430893
SW2: KEY2; Kailh_CPG151101S11_MX_Hotswap_Bottom; MPN Kailh CPG151101S11; LCSC C41430893

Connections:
/3V3: C1.2, J1.1, R1.1, R2.2, R3.2
/GND: C1.1, J1.2, R4.2, SW1.1, SW2.2
/ID: J1.5, R3.1, R4.1
/IN1: J1.3, R1.2, SW1.2
/IN2: J1.4, R2.1, SW2.1

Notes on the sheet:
Module connector pinout (same on every input module):
1 3V3 | 2 GND | 3 IN1 = GPIO10 | 4 IN2 = GPIO7 | 5 ID = GPIO8 | 6 GPIO6 | 7 GPIO4 | 8 GPIO2
MX V1: keys switch IN1/IN2 to GND (10k pull-ups). ID = 3V3 x 10k/(100k+10k) = 0.30 V.
Sockets, J1 and all passives are on the bottom side; the switches sit on top under the plate.

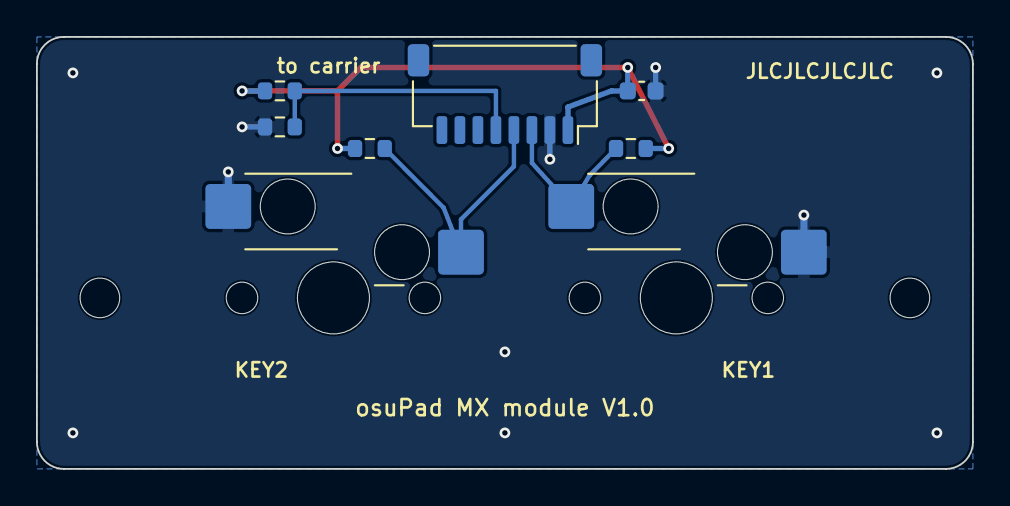
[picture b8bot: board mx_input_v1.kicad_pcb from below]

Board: 2 copper layers, 52.0 x 24.0 mm, 10 parts (8 on the bottom side), 5 nets.

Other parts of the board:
H1, H2: MountingHole_2.2mm_M2

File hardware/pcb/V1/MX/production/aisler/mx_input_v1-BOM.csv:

Reference,Quantity,Value,Footprint,MFG,MPN,LCSC,Side,Type
"R1,R2,R4",3,10k,R_0603_1608Metric,UNI-ROYAL,0603WAF1002T5E,C25804,bottom,SMD
"C1",1,100nF,C_0603_1608Metric,YAGEO,CC0603KRX7R9BB104,C14663,bottom,SMD
"J1",1,MODULE,JST_SH_SM08B-SRSS-TB_1x08-1MP_P1.00mm_Horizontal,JST,SM08B-SRSS-TB(LF)(SN),C160407,bottom,SMD
"R3",1,100k,R_0603_1608Metric,UNI-ROYAL,0603WAF1003T5E,C25803,bottom,SMD
"SW2",1,KEY2,Kailh_CPG151101S11_MX_Hotswap_Bottom,Kailh,CPG151101S11,C41430893,bottom,SMD
"SW1",1,KEY1,Kailh_CPG151101S11_MX_Hotswap_Bottom,Kailh,CPG151101S11,C41430893,bottom,SMD

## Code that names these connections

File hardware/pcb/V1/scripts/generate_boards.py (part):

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MODULE_PINOUT = {
    "1": "3V3",
    "2": "GND",
    "3": "IN1",    # GPIO10  KEY1 (MX)  / analog 1 (Hall)
    "4": "IN2",    # GPIO7   KEY2 (MX)  / analog 2 (Hall)
    "5": "ID",     # GPIO8   module ID voltage divider (ADC)
    "6": "IO6",    # GPIO6   spare, e.g. SPI MISO
    "7": "IO4",    # GPIO4   spare, e.g. SPI MOSI / CS
    "8": "IO2",    # GPIO2   spare, e.g. SPI SCK
}

JST = dict(symbol="Conn_01x08", footprint="JST_SH_SM08B-SRSS-TB_1x08-1MP_P1.00mm_Horizontal",
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
    write_schematic(directory, project, "OPad MX Input Module V1", parts, [
        "Module connector pinout (same on every input module):",
        "1 3V3 | 2 GND | 3 IN1 = GPIO10 | 4 IN2 = GPIO7 | 5 ID = GPIO8 | 6 GPIO6 | 7 GPIO4 | 8 GPIO2",
        "MX V1: keys switch IN1/IN2 to GND (10k pull-ups). ID = 3V3 x 10k/(100k+10k) = 0.30 V.",
        "Sockets, J1 and all passives are on the bottom side; the switches sit on top under the plate.",
    ])
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
    p1_nets = {1: "IO2", 2: "IO4", 3: "IO6", 8: "ID", 9: "IN2", 10: "IN1"}
    p2_nets = {1: "3V3", 2: "GND"}
    p1_names = ["GPIO2", "GPIO4", "GPIO6", "GPIO16", "GPIO17", "GPIO18", "GPIO21", "GPIO8", "GPIO7",
                "GPIO10", "GPIO20 USB_D+", "GPIO19 USB_D-", "GND", "5V"]
    p2_names = ["3V3", "GND", "GPIO43 TXD", "GPIO44 RXD", "GPIO47", "GPIO48", "GPIO15", "GPIO13",
                "GPIO11", "GPIO12", "GPIO14", "GPIO9", "GND", "VBAT"]

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
    notes = ["P1 header (GPIO names): " + ", ".join("%d %s" % (i + 1, n) for i, n in enumerate(p1_names)),
             "P2 header (GPIO names): " + ", ".join("%d %s" % (i + 1, n) for i, n in enumerate(p2_names)),
             "Module connector: 1 3V3 | 2 GND | 3 IN1 = GPIO10 | 4 IN2 = GPIO7 | 5 ID = GPIO8 | 6 GPIO6 | 7 GPIO4 | 8 GPIO2",
             "All six module signals are ADC1-capable (ADC continuous mode on the ESP32-S3 is ADC1 only).",
             "Passive carrier: the module ID divider lives on each input module."]
    write_schematic(directory, project, "OPad Controller Carrier V1", parts, notes)
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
